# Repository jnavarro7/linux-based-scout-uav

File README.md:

# linux-based-scout-uav
 Linux based scout UAV

 LinuxベースのスカウトUAV

# What it is:
Hobby project to create a UAV (Unmanned aerial vehicle) in a quadcopter drone format, based on the OSD32MP1 SiP which is a Linux capable system. 

Linux 対応システムである OSD32MP1 SiP をベースに、クアッドコプター ドローン形式の UAV (無人航空機) を作成する趣味のプロジェクト。

# Requirements & components

# Block diagram

The system block diagram is still a work in progress.
Still looking for a good option on ESC (electronic speed controller) for the drone. Maybe CAN bus based systems can be used as there is a CAN bus available in the OSD32MP1 SiP. 

System block diagram

# Software/Firmware 

## Operating system 

Octavo develops and mantains a Debian based image that supports their development boards.  I plan to start prototyping with this image. 

## Device tree

I will base my work on Octavo's OSD32MP1-BRK device tree and modify it as needed. 

# Hardware 

## OSD32MP1 SiP

Based on the OSD32MP1: 

    ST32MP15x Features:
    Arm® Cortex®-A7 up to 800MHz x2
    Arm® Cortex®-M4 up to 209MHz
    NEON™SIMD Coprocessor x2
    USB 2.0 HS + PHY x2
    Ethernet 10/100/1000
    CAN FD/TTCAN x2, UART x4, USART x4,SPI x6, I2C x6, SAI x4, QSPI, SPDIF, I2S x3
    eMMC/SD/SDIO Ports x3
    GPIO x148
    24-bit RGB Display, MIPI DSI
    Camera Interface
    22 Channel 16-bit ADC x2, 12-bit DAC x2
 
The SiP has an embedded ARM Cortex M4 sub-system which can be used by creating firmware in ST Cube IDE. 

## Schematic capture

Started working on the schematic capture, schematic in PDF format will be added as it is updated. 

## Board placement/layout 

Started work on board by trying board shapes and importing the DXF files. Already placed the initial components available, will update as needed. 

## EDA

Hardware being designed in KiCad 8.0

# License

Released under the Creative Commons Attribution 4.0 License
https://creativecommons.org/licenses/by/4.0/

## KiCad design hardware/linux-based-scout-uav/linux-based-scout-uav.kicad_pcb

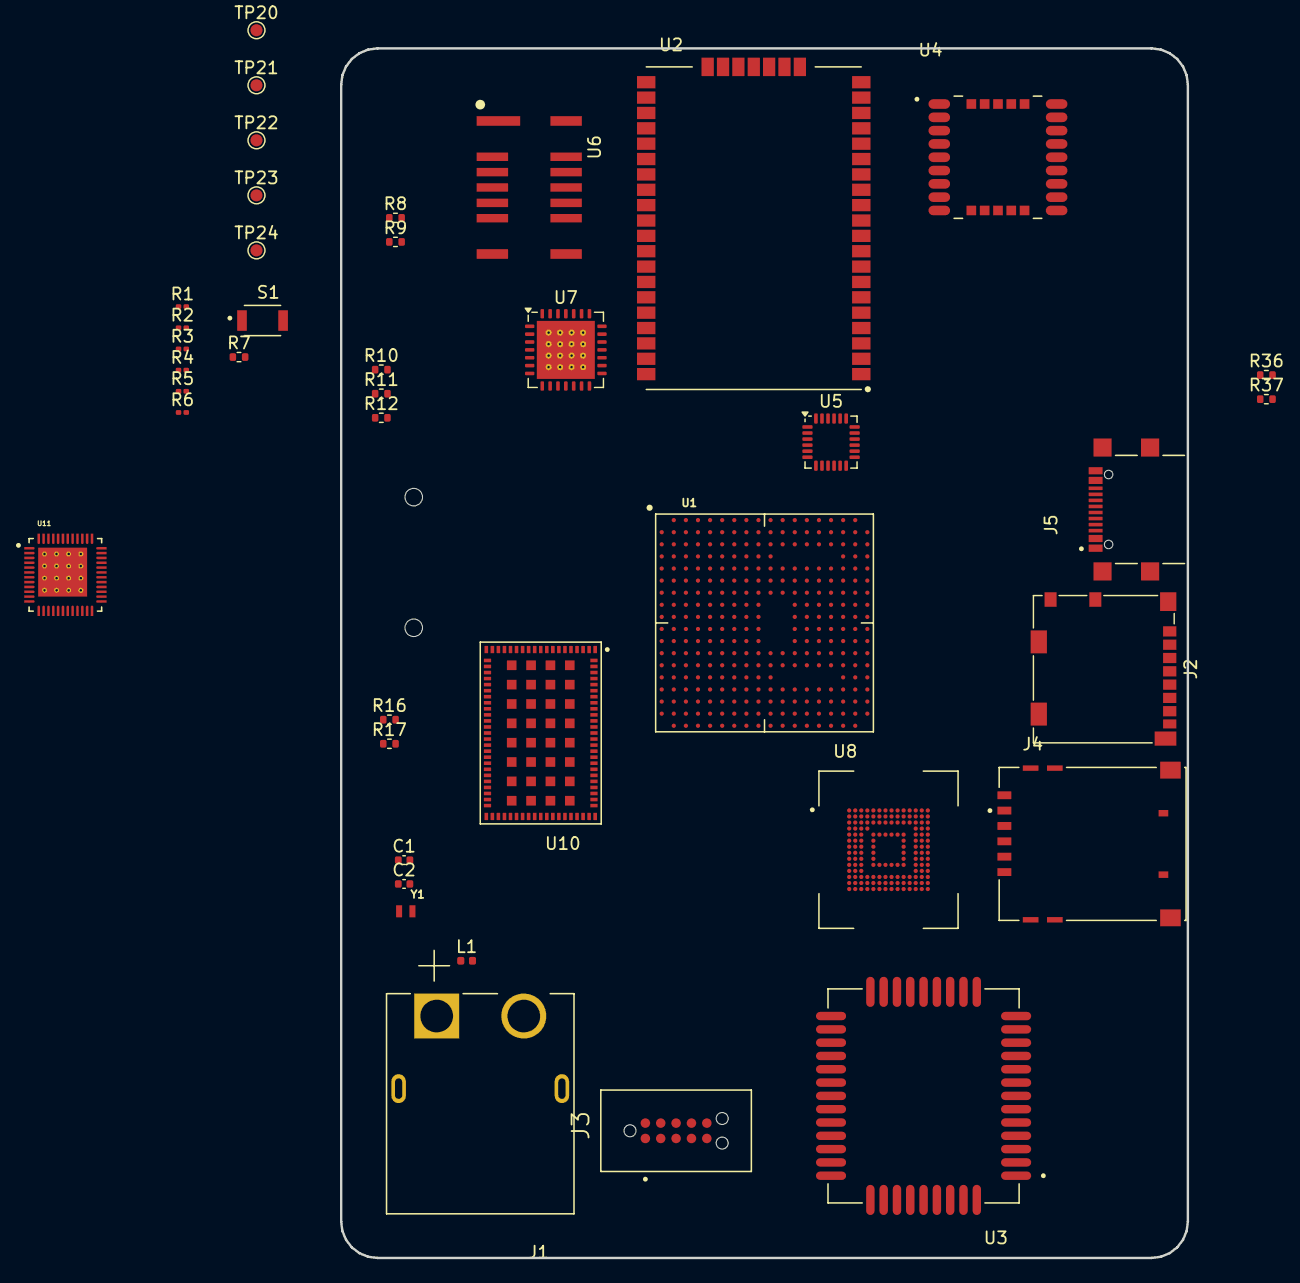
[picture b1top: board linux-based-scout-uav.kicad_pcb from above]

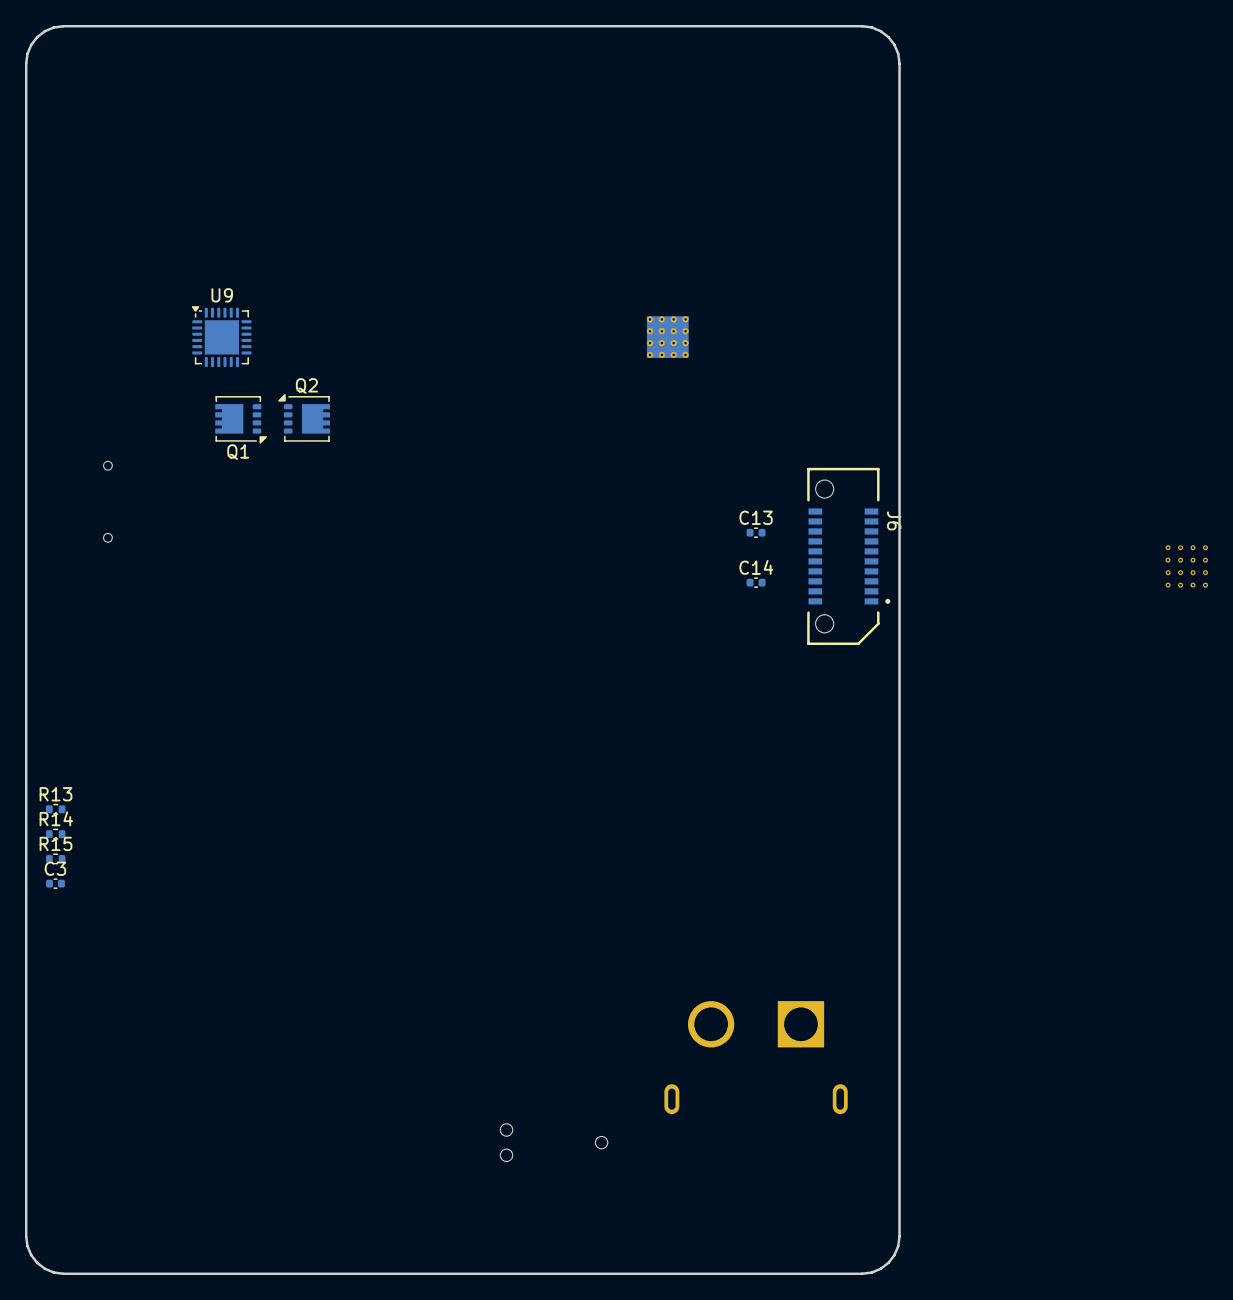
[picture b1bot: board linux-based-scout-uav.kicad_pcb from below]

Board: 2 copper layers, 70.0 x 100.0 mm, 51 parts (10 on the bottom side), 79 nets, no tracks yet.

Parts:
C1, C2: 12pF; C_0402_1005Metric
C3, C13, C14: 100nF; C_0402_1005Metric
J1: XT60PW-M; AMASS_XT60PW-M
J2: Micro_SD_Card_Det2; microSD_HC_Molex_104031-0811
J3: TC2050-IDC-NL; TAG-CONNECT_TC2050-IDC-NL
J4: 0786463001; MOLEX_0786463001
J5: GSB1C41110SSHR; AMPHENOL_GSB1C41110SSHR
J6: ERF8-010-05.0-L-DV-K-TR; SAMTEC_ERF8-010-05.0-L-DV-K-TR
L1: L; L_0402_1005Metric
Q1, Q2: DMP3013SFV; Diodes_PowerDI3333-8
R1, R2, R3, R4, R5, R6: 10K; R_0201_0603Metric
R7, R10, R16, R17, R37: 10K; R_0402_1005Metric
R8, R9: Jumper; R_0402_1005Metric
R11, R12: 10K DNP; R_0402_1005Metric
R13, R14, R15: 22R; R_0402_1005Metric
R36: 49.9K; R_0402_1005Metric
S1: B3U-1000P; SW_B3U-1000P
TP20, TP21, TP22, TP23, TP24: TestPoint; TestPoint_Pad_D1.0mm
U1: OSD32MP157C-512M-IAA; OSD32MP15X-BGA-324
U2: RN2903A-I_RM098; XCVR_RN2903A-I_RM098
U3: M65; XCVR_M65
U4: LC76G; XCVR_LC76G
U5: MPU-6050; InvenSense_QFN-24_4x4mm_P0.5mm
U6: AMG8833; XDCR_AMG8833
U7: SX1272; QFN-28-1EP_6x6mm_P0.65mm_EP4.8x4.8mm_ThermalVias
U8: EMMC04G-W627-M06U; BGA153N50P14X14_1300X1150X100N
U9: CYPD3177-24LQ; QFN-24-1EP_4x4mm_P0.5mm_EP2.75x2.75mm
U10: G313-06329-00; MODULE_G313-06329-00
U11: TPS65217CRSLR; IC_TPS65217CRSLR
Y1: ABS05-32.768KHZ-7-T; XTAL_ABS05-32.768KHZ-7-T

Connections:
+3V3: J2.4 (VDD), J3.1, R1.1, R2.1, R3.1, R4.1, R5.1, R6.1, R10.1, R16.1, R17.1, U1.H3 (PMIC_VOUT4_1), U1.J3 (PMIC_VOUT4_2), U5.13 (VDD), U8.C6 (VCCQ), U8.E6 (VCC), U8.F5 (VCC), U8.J10 (VCC), U8.K9 (VCC), U8.M4 (VCCQ), U8.N4 (VCCQ), U8.P3 (VCCQ), U8.P5 (VCCQ)
+BST: U1.J8 (PMIC_BSTOUT_1), U1.J9 (PMIC_BSTOUT_2)
+VBUS: J5.A4_B9 (VBUS_A), J5.B4_A9 (VBUS_B), Q1.5 (D), R37.1, U9.18 (VBUS_IN)
+VIN: U1.G1 (VIN_1), U1.G2 (VIN_3), U1.G3 (PMIC_LDO25IN), U1.H1 (VIN_2), U1.H2 (VIN_4), U1.H8 (PMIC_SWIN_1), U1.H9 (PMIC_SWIN_2), U1.L8 (PMIC_BSTIN_1), U1.L9 (PMIC_BSTIN_3), U1.M8 (PMIC_BSTIN_2), U1.M9 (PMIC_BSTIN_4)
+VSW: U1.G9 (PMIC_SWOUT_1), U1.G10 (PMIC_SWOUT_2)
/google-tpu-coral-1/H_PCIE_TX_N: C14.1, U10.4 (PCIE_TX_N)
/google-tpu-coral-1/H_PCIE_TX_P: C13.1, U10.5 (PCIE_TX_P)
/osd32mp1-2/SWCLK/TCK: J3.4, U1.R15 (JTCK-SWCLK)
/osd32mp1-2/SWDIO/TMS: J3.2, U1.R14 (JTMS-SWDIO)
/osd32mp1-2/SWO/TDO: J3.6, U1.R12 (JTDO-TRACESWO)
/osd32mp1-2/TDI: J3.8, U1.R13 (JTDI)
/osd32mp1-2/~TRST: J3.9, U1.R11 (NJTRST)
/power-section-1/CC2: J5.B5 (CC2), U9.14 (CC2)
/quectel-m65-1/SIM_CLK: J4.C3 (CLK), R14.1
/quectel-m65-1/SIM_DATA: J4.C7 (I/O), R13.1
/quectel-m65-1/SIM_RST: J4.C2 (RST), R15.1
/quectel-m65-1/SIM_VDD: C3.1, J4.C1 (VCC), U3.14 (SIM_VDD)
GND: C1.2, C2.2, C3.2, J1.2 (-), J2.6 (VSS), J2.10 (DET_A), J2.11 (SHIELD), J3.3, J4.C5 (GND), J4.G1 (GND), J4.G2 (GND), J4.G3 (GND), J4.G4 (GND), J4.G5 (GND), J4.G6 (GND), J5.A1_B12 (GND_A), J5.B1_A12 (GND_B), J5.SH1 (SHIELD), J5.SH2 (SHIELD), J5.SH3 (SHIELD), J5.SH4 (SHIELD), J6.01, J6.02, J6.08, J6.14, J6.19, J6.20, R11.2, S1.1, U1.D4 (VSS_1), U1.E4 (VSS_2), U1.E5 (VSS_4), U1.E6 (VSS_14), U1.E7 (VSS_18), U1.E8 (VSS_22), U1.E9 (VSS_26), U1.E10 (VSS_29), U1.E11 (VSS_32), U1.E12 (VSS_37), U1.E13 (VSS_42), U1.E14 (VSS_51), U1.E15 (VSS_60), U1.F4 (VSS_3), U1.F5 (VSS_5), U1.F6 (VSS_15), U1.F7 (VSS_19), U1.F8 (VSS_23), U1.F9 (VSS_27), U1.F10 (VSS_30), U1.F11 (VSS_33), U1.F12 (VSS_38), U1.F13 (VSS_43), U1.F14 (VSS_52), U1.F15 (VSS_61), U1.G5 (VSS_6), U1.G11 (VSS_34), U1.G12 (VSS_39), U1.G13 (VSS_44), U1.G14 (VSS_53), U1.G15 (VSS_62), U1.H5 (VSS_7), U1.H13 (VSS_45), U1.H14 (VSS_54), U1.H15 (VSS_63), U1.J1 (HSE_OSC_OEN), U1.J5 (VSS_8), U1.J13 (VSS_46), U1.J14 (VSS_55), U1.J15 (VSS_64), U1.J16 (VSS_69), U1.K5 (VSS_9), U1.K13 (VSS_47), U1.K14 (VSS_56), U1.K15 (VSS_65), U1.K16 (VSS_70), U1.L5 (VSS_10), U1.L13 (VSS_48), U1.L14 (VSS_57), U1.L15 (VSS_66), U1.M5 (VSS_11), U1.M10 (BYPASS_REG1V8), U1.M11 (VSS_35), U1.M12 (VSS_40), U1.M13 (VSS_49), U1.M14 (VSS_58), U1.M15 (VSS_67), U1.N5 (VSS_12), U1.N6 (VSS_16), U1.N7 (VSS_20), U1.N8 (VSS_24), U1.N9 (VSS_28), U1.N10 (VSS_31), U1.N11 (VSS_36), U1.N12 (VSS_41), U1.N13 (VSS_50), U1.N14 (VSS_59), U1.N15 (VSS_68), U1.P5 (VSS_13), U1.P6 (VSS_17), U1.P7 (VSS_21), U1.P8 (VSS_25), U2.1 (GND), U2.8 (GND), U2.11 (GND), U2.20 (GND), U2.21 (GND), U2.22 (GND), U2.24 (GND), U2.26 (GND), U2.27 (GND), U2.28 (GND), U2.33 (GND), U2.41 (GND), U2.47 (GND), U3.1 (AGND), U3.10 (SIM_GND), U3.27 (GND), U3.34 (GND), U3.36 (GND), U3.37 (GND), U3.40 (GND), U3.41 (GND), U4.1 (GND), U4.10 (GND), U4.12 (GND), U4.28 (GND), U5.18 (GND), U6.6 (GND), U7.16 (GND), U7.22 (GND), U7.26 (GND), U7.29 (GND), U8.A6 (VSS), U8.C4 (VSSQ), U8.E7 (VSS), U8.G5 (VSS), U8.H10 (VSS), U8.J5 (VSS), U8.K8 (VSS), U8.N2 (VSSQ), U8.N5 (VSSQ), U8.P4 (VSSQ), U8.P6 (VSSQ), U9.19 (GND), U9.22 (GND), U9.25 (GND), U10.1 (GND), U10.2 (GND), U10.3 (GND), U10.6 (GND), U10.9 (GND), U10.12 (GND), U10.15 (GND), U10.16 (GND), U10.17 (GND), U10.18 (GND), U10.19 (GND), U10.20 (GND), U10.21 (GND), U10.22 (GND), U10.23 (GND), U10.24 (GND), U10.25 (GND), U10.26 (GND), U10.27 (GND), U10.28 (GND), U10.29 (GND), U10.30 (GND), U10.31 (GND), U10.32 (GND), U10.33 (GND), U10.34 (GND), U10.35 (GND), U10.36 (GND), U10.38 (GND), U10.39 (GND), U10.40 (GND), U10.41 (GND), U10.42 (GND), U10.43 (GND), U10.44 (GND), U10.45 (GND), U10.46 (GND), U10.47 (GND), U10.48 (GND), U10.51 (GND), U10.55 (GND), U10.68 (GND), U10.69 (GND), U10.70 (GND), U10.71 (GND), U10.72 (GND), U10.73 (GND), U10.74 (GND), U10.75 (GND), U10.79 (GND), U10.80 (GND), U10.81 (GND), U10.86 (GND), U10.87 (GND), U10.88 (GND), U10.89 (GND), U10.90 (GND), U10.91 (GND), U10.92 (GND), U10.93 (GND), U10.94 (GND), U10.95 (GND), U10.96 (GND), U10.97 (GND), U10.98 (GND), U10.99 (GND), U10.100 (GND), U10.101 (GND), U10.102 (GND), U10.103 (GND), U10.104 (GND), U10.105 (GND), U10.106 (GND), U10.107 (GND), U10.108 (GND), U10.109 (GND), U10.110 (GND), U10.111 (GND), U10.112 (GND), U10.113 (GND), U10.114 (GND), U10.115 (GND), U10.116 (GND), U10.117 (GND), U10.118 (GND), U10.119 (GND), U10.120 (GND), U11.30 (PGND), U11.41 (AGND), U11.49 (PGND), U11.50 (PGND), U11.51 (PGND), U11.52 (PGND), U11.53 (PGND), U11.54 (PGND), U11.55 (PGND), U11.56 (PGND), U11.57 (PGND), U11.58 (PGND), U11.59 (PGND), U11.60 (PGND), U11.61 (PGND), U11.62 (PGND), U11.63 (PGND), U11.64 (PGND), U11.65 (PGND)
I2C1_SCL: R17.2, U1.H18 (PB6), U5.23 (SCL), U6.3 (SCL)
I2C1_SDA: R16.2, U1.V12 (PB7), U5.24 (SDA), U6.2 (SDA)
MMC2_CLK: U1.T12 (PE3), U8.M6 (CLK)
MMC2_CMD: U1.U15 (PG6), U8.M5 (CMD)
MMC2_D0: U1.T14 (PB14), U8.A3 (DAT0)
MMC2_D1: U1.V13 (PB15), U8.A4 (DAT1)
MMC2_D2: U1.V14 (PB3), U8.A5 (DAT2)
MMC2_D3: U1.U14 (PB4), U8.B2 (DAT3)
MMC2_D4: U1.T17 (PA8), U8.B3 (DAT4)
MMC2_D5: U1.U12 (PA9), U8.B4 (DAT5)
MMC2_D6: U1.V15 (PE5), U8.B5 (DAT6)
MMC2_D7: U1.R16 (PC7), U8.B6 (DAT7)
unnamed: Q1.4 (G), Q2.4 (G), R36.2, R37.2
unnamed: Q1.1 (S), Q1.2 (S), Q1.3 (S), Q2.1 (S), Q2.2 (S), Q2.3 (S), R36.1
unnamed: C1.1, U1.N2 (PC14-OSC32_IN), Y1.2
unnamed: C2.1, U1.N1 (PC15-OSC32_OUT), Y1.1
unnamed: R8.1, U1.M1 (VDDA)
unnamed: R8.2, U1.M2 (VREF+)
unnamed: R9.1, U1.K2 (VREF-)
unnamed: R9.2, U1.K1 (VSSA)
unnamed: TP20.1, U2.35 (GPIO0)
unnamed: TP21.1, U2.36 (GPIO1)
unnamed: TP22.1, U2.37 (GPIO2)
unnamed: TP23.1, U2.38 (GPIO3)
unnamed: TP24.1, U2.39 (GPIO4)
unnamed: U2.12 (VDD), U2.34 (VDD)
unnamed: R14.2, U3.13 (SIM_CLK)
unnamed: R13.2, U3.11 (SIM_DATA)
unnamed: R15.2, U3.12 (SIM_RST)
unnamed: U3.42 (VBAT), U3.43 (VBAT)
unnamed: R10.2, R11.1, U6.5 (AD_SELECT)
unnamed: R12.2, U6.4 (INT)
unnamed: L1.1, U7.27 (PA_BOOST)
unnamed: U8.A1 (NC_1), U8.A2 (NC_1), U8.A8 (NC_1), U8.A9 (NC_1), U8.A10 (NC_1), U8.A11 (NC_1), U8.A12 (NC_1), U8.A13 (NC_1), U8.A14 (NC_1), U8.B1 (NC_1), U8.B7 (NC_1), U8.B8 (NC_1), U8.B9 (NC_1), U8.B10 (NC_1)
unnamed: U8.B11 (NC_2), U8.B12 (NC_2), U8.B13 (NC_2), U8.B14 (NC_2), U8.C1 (NC_2), U8.C3 (NC_2), U8.C5 (NC_2), U8.C7 (NC_2), U8.C8 (NC_2), U8.C9 (NC_2), U8.C10 (NC_2), U8.C11 (NC_2), U8.C12 (NC_2), U8.C13 (NC_2), U8.C14 (NC_2)
unnamed: U8.D1 (NC_3), U8.D2 (NC_3), U8.D3 (NC_3), U8.D4 (NC_3), U8.D12 (NC_3), U8.D13 (NC_3), U8.D14 (NC_3), U8.E1 (NC_3), U8.E2 (NC_3), U8.E3 (NC_3), U8.E12 (NC_3), U8.E13 (NC_3)
unnamed: U8.E14 (NC_4), U8.F1 (NC_4), U8.F2 (NC_4), U8.F3 (NC_4), U8.F12 (NC_4), U8.F13 (NC_4), U8.F14 (NC_4), U8.G1 (NC_4), U8.G2 (NC_4), U8.G12 (NC_4), U8.G13 (NC_4), U8.G14 (NC_4)
unnamed: U8.H1 (NC_5), U8.H2 (NC_5), U8.H3 (NC_5), U8.H12 (NC_5), U8.H13 (NC_5), U8.H14 (NC_5), U8.J1 (NC_5), U8.J2 (NC_5), U8.J3 (NC_5), U8.J12 (NC_5), U8.J13 (NC_5), U8.J14 (NC_5), U8.K1 (NC_5), U8.K2 (NC_5), U8.K3 (NC_5)
unnamed: U8.K12 (NC_6), U8.K13 (NC_6), U8.K14 (NC_6), U8.L1 (NC_6), U8.L2 (NC_6), U8.L3 (NC_6), U8.L12 (NC_6), U8.L13 (NC_6), U8.L14 (NC_6), U8.M1 (NC_6), U8.M2 (NC_6), U8.M3 (NC_6), U8.M7 (NC_6)
unnamed: U8.M8 (NC_7), U8.M9 (NC_7), U8.M10 (NC_7), U8.M11 (NC_7), U8.M12 (NC_7), U8.M13 (NC_7), U8.M14 (NC_7), U8.N1 (NC_7), U8.N3 (NC_7), U8.N6 (NC_7), U8.N7 (NC_7), U8.N8 (NC_7), U8.N9 (NC_7), U8.N10 (NC_7)
unnamed: U8.N11 (NC_8), U8.N12 (NC_8), U8.N13 (NC_8), U8.N14 (NC_8), U8.P1 (NC_8), U8.P2 (NC_8), U8.P8 (NC_8), U8.P9 (NC_8), U8.P11 (NC_8), U8.P12 (NC_8), U8.P13 (NC_8), U8.P14 (NC_8)
unnamed: U10.56 (VIN), U10.57 (VIN), U10.58 (VIN), U10.59 (VIN), U10.60 (VIN), U10.61 (VIN), U10.62 (VIN), U10.63 (VIN), U10.64 (VIN), U10.65 (VIN), U10.66 (VIN), U10.67 (VIN)
unnamed: U11.4 (BAT), U11.5 (BAT)
unnamed: U11.7 (SYS), U11.8 (SYS)
PCIE_REFCLK_N: J6.16, U10.10 (PCIE_REFCLK_N)
PCIE_REFCLK_P: J6.18, U10.11 (PCIE_REFCLK_P)
PCIE_RX_N: J6.04, U10.8 (PCIE_RX_N)
PCIE_RX_P: J6.06, U10.7 (PCIE_RX_P)
PCIE_TX_N: C14.2, J6.12
PCIE_TX_P: C13.2, J6.10
SDMMC1_CK: J2.5 (CLK), R4.2
SDMMC1_CMD: J2.3 (CMD), R3.2, U1.U18 (PD2), U1.V17 (PC12)
SDMMC1_D0: J2.7 (DAT0), R5.2, U1.T16 (PC8)
SDMMC1_D1: J2.8 (DAT1), R6.2, U1.U16 (PC9)
SDMMC1_D2: J2.1 (DAT2), R1.2, U1.V16 (PC10)
SDMMC1_D3: J2.2 (DAT3/CD), R2.2, U1.U17 (PC11)
USB_2_DN: U1.J17 (USB_DM2), U10.14 (USB2_D_N)
USB_2_DP: U1.J18 (USB_DP2), U10.13 (USB2_D_P)
USB_DP: J5.A6 (DP1), U1.K17 (USB_DP1)
VDDI: R7.1, U1.G7 (VDD_1), U1.H7 (VDD_2), U1.J7 (VDD_3), U1.K4 (VDD_7), U1.K7 (VDD_4), U1.L4 (VDD_8), U1.L7 (VDD_5), U1.M4 (VDD_9), U1.M7 (VDD_6)
~RESET: J3.10, R7.2, S1.2, U1.M3 (NRST)

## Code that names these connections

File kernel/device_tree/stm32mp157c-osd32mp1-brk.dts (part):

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	u-boot,dm-pre-reloc;
	i2c1_pins_mx: i2c1-0 {
		pins {
			pinmux = <STM32_PINMUX('H', 11, AF5)>, /* I2C1_SCL */
				 <STM32_PINMUX('H', 12, AF5)>; /* I2C1_SDA */
			bias-disable;
			drive-open-drain;
			slew-rate = <0>;
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
	i2c1_pins_sleep_mx: i2c1-1 {
		pins {
			pinmux = <STM32_PINMUX('H', 11, ANALOG)>, /* I2C1_SCL */
				 <STM32_PINMUX('H', 12, ANALOG)>; /* I2C1_SDA */
		};
	};

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		u-boot,dm-pre-reloc;
		pins1 {
			u-boot,dm-pre-reloc;
			pinmux = <STM32_PINMUX('C', 8, AF12)>, /* SDMMC1_D0 */
					 <STM32_PINMUX('C', 9, AF12)>, /* SDMMC1_D1 */
					 <STM32_PINMUX('C', 10, AF12)>, /* SDMMC1_D2 */
					 <STM32_PINMUX('C', 11, AF12)>, /* SDMMC1_D3 */
					 <STM32_PINMUX('D', 2, AF12)>; /* SDMMC1_CMD */
			bias-disable;
			drive-push-pull;
			slew-rate = <1>;
		};
		pins2 {
			u-boot,dm-pre-reloc;
			pinmux = <STM32_PINMUX('C', 12, AF12)>; /* SDMMC1_CK */
			bias-disable;
			drive-push-pull;
			slew-rate = <2>;
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		u-boot,dm-pre-reloc;
		pins1 {
			u-boot,dm-pre-reloc;
			pinmux = <STM32_PINMUX('C', 8, AF12)>, /* SDMMC1_D0 */
					 <STM32_PINMUX('C', 9, AF12)>, /* SDMMC1_D1 */
					 <STM32_PINMUX('C', 10, AF12)>, /* SDMMC1_D2 */
					 <STM32_PINMUX('C', 11, AF12)>; /* SDMMC1_D3 */
			bias-disable;
			drive-push-pull;
			slew-rate = <1>;
		};
		pins2 {
			u-boot,dm-pre-reloc;
			pinmux = <STM32_PINMUX('C', 12, AF12)>; /* SDMMC1_CK */
			bias-disable;
			drive-push-pull;
			slew-rate = <2>;
		};
		pins3 {
			u-boot,dm-pre-reloc;
			pinmux = <STM32_PINMUX('D', 2, AF12)>; /* SDMMC1_CMD */
			bias-disable;
			drive-open-drain;
			slew-rate = <1>;
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		u-boot,dm-pre-reloc;
		pins {
			u-boot,dm-pre-reloc;
			pinmux = <STM32_PINMUX('C', 8, ANALOG)>, /* SDMMC1_D0 */
					 <STM32_PINMUX('C', 9, ANALOG)>, /* SDMMC1_D1 */
					 <STM32_PINMUX('C', 10, ANALOG)>, /* SDMMC1_D2 */
					 <STM32_PINMUX('C', 11, ANALOG)>, /* SDMMC1_D3 */
					 <STM32_PINMUX('C', 12, ANALOG)>, /* SDMMC1_CK */
					 <STM32_PINMUX('D', 2, ANALOG)>; /* SDMMC1_CMD */
		};
	};

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
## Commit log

2024-06-29 Initial commit
    Initial commit
2024-06-30 Readme.md update
    Readme file update.
2024-06-30 Schematic update
    Schematic updates on battery connector and OSD32MP1 power section.
2024-06-30 Readme update
    Readme update.
2024-07-01 Updates (Schematic, Readme, doc)
    Updates to Schematic capture, README file and doc files.
2024-07-02 Updates (schematic, readme, doc files, device tree)
    Updates to schematic, readme file and doc files.
2024-07-04 schematic update
2024-07-05 Updates; schematic, readme, doc files
    Schematic, readme and doc files updates.
2024-07-05 Schematic updates
2024-07-06 Readme, doc files update.
2024-07-06 Schematic, board update
2024-07-06 board, shchematic PDF update
2024-07-06 Readme update.
2024-07-06 Readme update
2024-07-12 Shcematic, board update.
2024-07-23 Schematic update - eMMC added
2024-08-06 Schematic update
    Work around I2C sensors
2024-11-01 Updated project to KiCAD 8.0.6
2024-12-05 Schematic update
    Work done on the USB-C receptacle and power delivery section.
2024-12-05 Schematic update USB DP section
    USB DP section updated, voltage and current setting resistor divider.
2024-12-08 schematic update
    schematic update
2024-12-09 Schematic/board update
2025-01-10 Board placement update
2025-01-14 Schematic and board update
2025-01-15 Schematic update - added Google Coral
    Google Coral edge TPU added to schematic
2025-01-31 Added TPS65217C PMIC
2025-02-27 Updated project to KiCad 9.0
2025-04-17 Update
    Update

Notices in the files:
kernel/device_tree/stm32mp157c-osd32mp1-brk.dts:
SPDX-License-Identifier: (GPL-2.0+ OR BSD-3-Clause)
Copyright (C) Octavo Systems LLC 2020 - All Rights Reserved
